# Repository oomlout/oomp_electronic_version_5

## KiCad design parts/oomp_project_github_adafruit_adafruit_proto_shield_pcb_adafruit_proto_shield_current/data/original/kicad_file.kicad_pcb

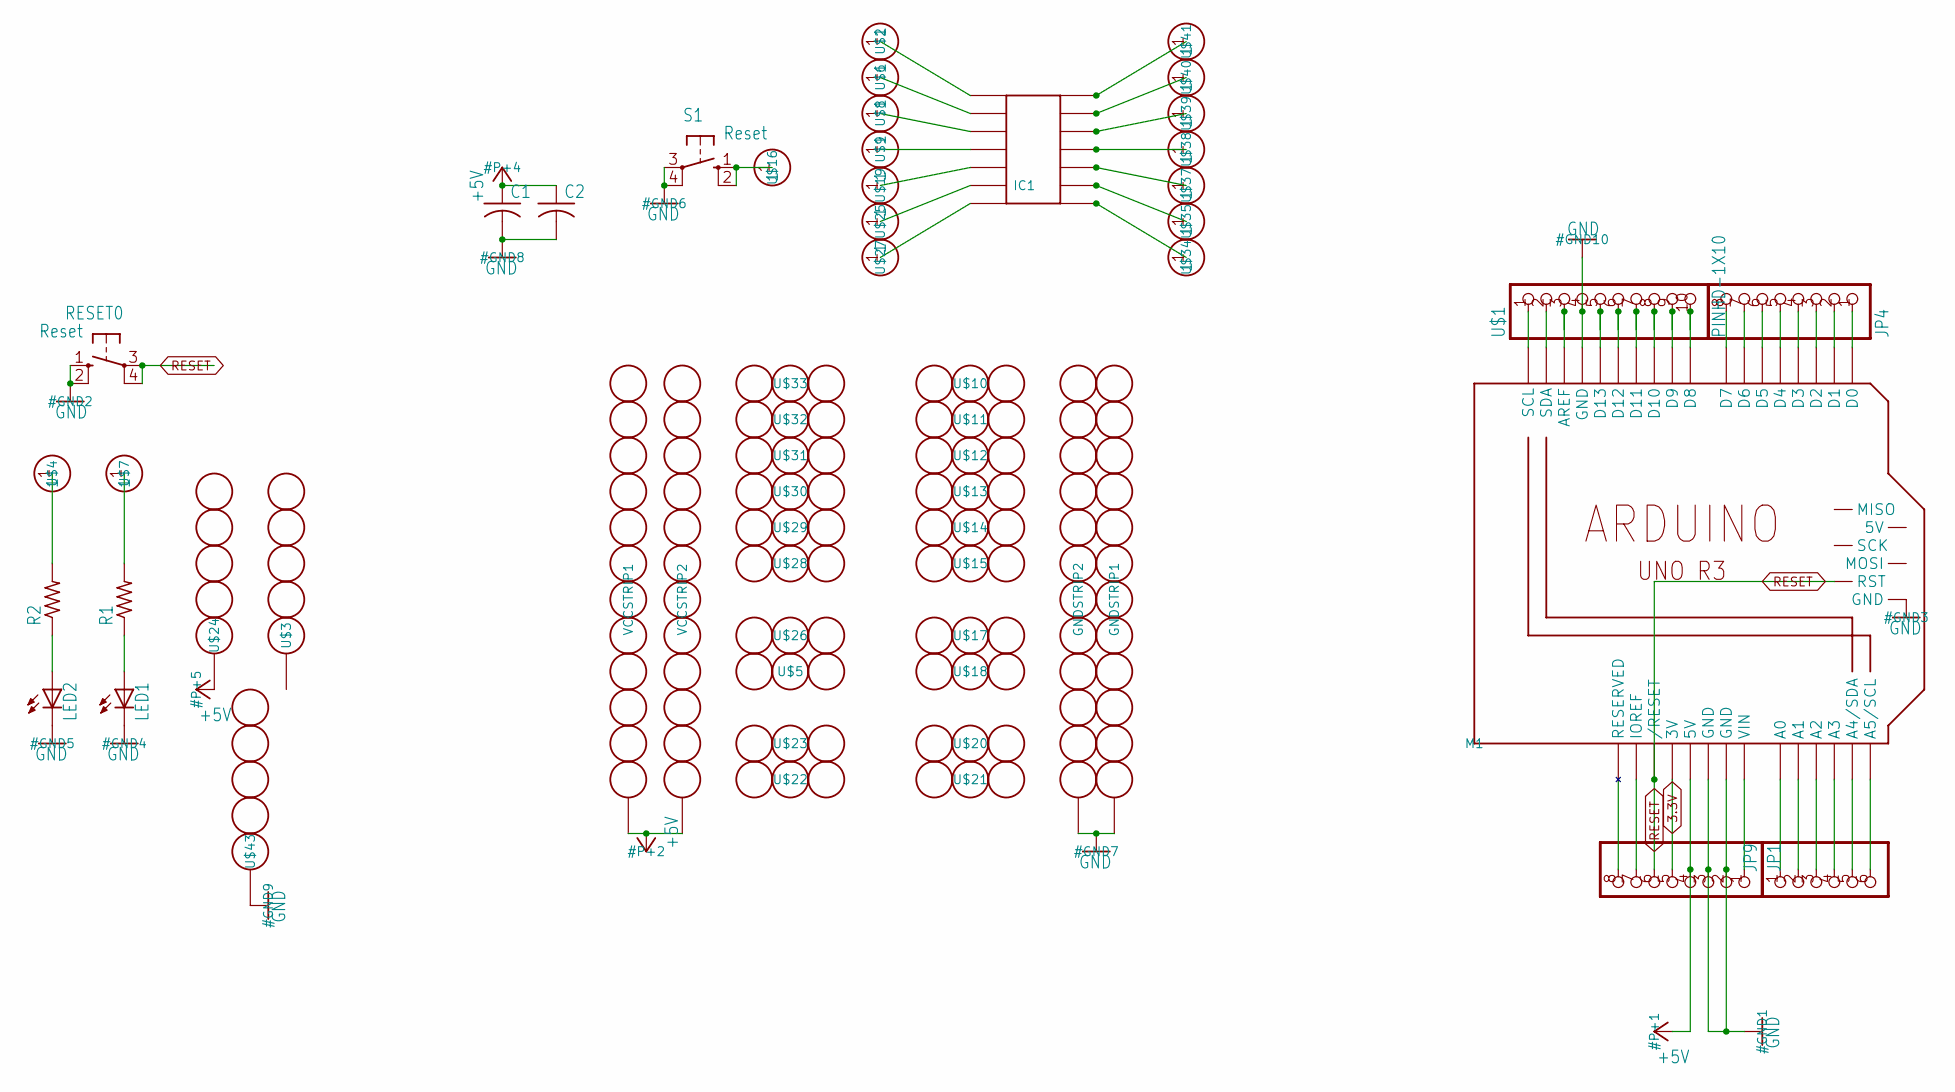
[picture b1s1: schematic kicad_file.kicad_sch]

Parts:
C1, C2: C-US025-025X050; C025-025X050
GNDSTRIP1, GNDSTRIP2: 12-STRIP
IC1: SMD-14; SO-14NMW
JP1, JP4: PINHD-1X8BIG; 1X08-BIG
JP9: PINHD-1X6B; 1X06-BIG
LED1, LED2: LED3MM
M1: ARDUINO_R3_ICSP; ARDUINOR3_ICSP
R1, R2: R-US_0207/5V; 0207_5V
RESET0: Reset; B3F-10XX
S1: Reset; B3F-10XX
U$1: PINHD-1X10; 1X10-BIG
U$2, U$4, U$6, U$7, U$8, U$9, U$16, U$19, U$25, U$27, U$34, U$35, U$37, U$38, U$39, U$40, U$41: PERFHOLE
U$3, U$24, U$43: 5-STRIP
U$5, U$10, U$11, U$12, U$13, U$14, U$15, U$17, U$18, U$20, U$21, U$22, U$23, U$26, U$28, U$29, U$30, U$31, U$32, U$33: 3-STRIP
VCCSTRIP1, VCCSTRIP2: 12-STRIP

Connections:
3.3V: JP1.5, M1.3V
+5V: C1.1, C2.1, JP1.4, M1.5V, U$24.P$3, VCCSTRIP1.P$1, VCCSTRIP2.P$1
GND: C1.2, C2.2, GNDSTRIP1.P$1, GNDSTRIP2.P$1, JP1.2, JP1.3, LED1.K (C), LED2.K (C), M1.GND, M1.GND@1 (GND), M1.GND@2 (GND), M1.GND@3 (GND), RESET0.1 (S), RESET0.2 (S1), S1.3, S1.4 (P1), U$1.4, U$43.P$3
unnamed: M1.AREF, U$1.3
unnamed: JP1.8, M1.RESERVED
unnamed: M1.D13, U$1.5
unnamed: LED1.A, R1.1
unnamed: JP1.7, M1.IOREF
unnamed: R1.2, U$7.1
unnamed: R2.2, U$4.1
unnamed: LED2.A, R2.1
unnamed: M1.D12, U$1.6
unnamed: M1.D11, U$1.7
unnamed: M1.D10, U$1.8
unnamed: M1.D9, U$1.9
unnamed: M1.D8, U$1.10
unnamed: JP9.1, M1.A0
unnamed: JP9.2, M1.A1
unnamed: JP9.3, M1.A2
unnamed: JP9.4, M1.A3
unnamed: JP9.5, M1.A4 (A4/SDA)
unnamed: JP9.6, M1.A5 (A5/SCL)
unnamed: JP4.1, M1.D0
unnamed: JP4.2, M1.D1
unnamed: JP4.3, M1.D2
unnamed: JP4.4, M1.D3
unnamed: JP4.5, M1.D4
unnamed: IC1.P$1, U$2.1
unnamed: IC1.P$2, U$6.1
unnamed: JP4.6, M1.D5
unnamed: JP4.7, M1.D6
unnamed: IC1.P$3, U$8.1
unnamed: IC1.P$4, U$9.1
unnamed: IC1.P$5, U$19.1
unnamed: JP4.8, M1.D7
unnamed: JP1.1, M1.VIN
unnamed: M1.SCL, U$1.1
unnamed: IC1.P$6, U$25.1
unnamed: IC1.P$7, U$27.1
unnamed: IC1.P$8, U$34.1
unnamed: IC1.P$9, U$35.1
unnamed: IC1.P$10, U$37.1
unnamed: M1.SDA, U$1.2
unnamed: IC1.P$11, U$38.1
unnamed: IC1.P$12, U$39.1
unnamed: IC1.P$13, U$40.1
unnamed: IC1.P$14, U$41.1
unnamed: S1.1 (S), S1.2 (S1), U$16.1
RESET: JP1.6, M1.RESET (/RESET), M1.RESET_ICSP (RST), RESET0.3, RESET0.4 (P1)

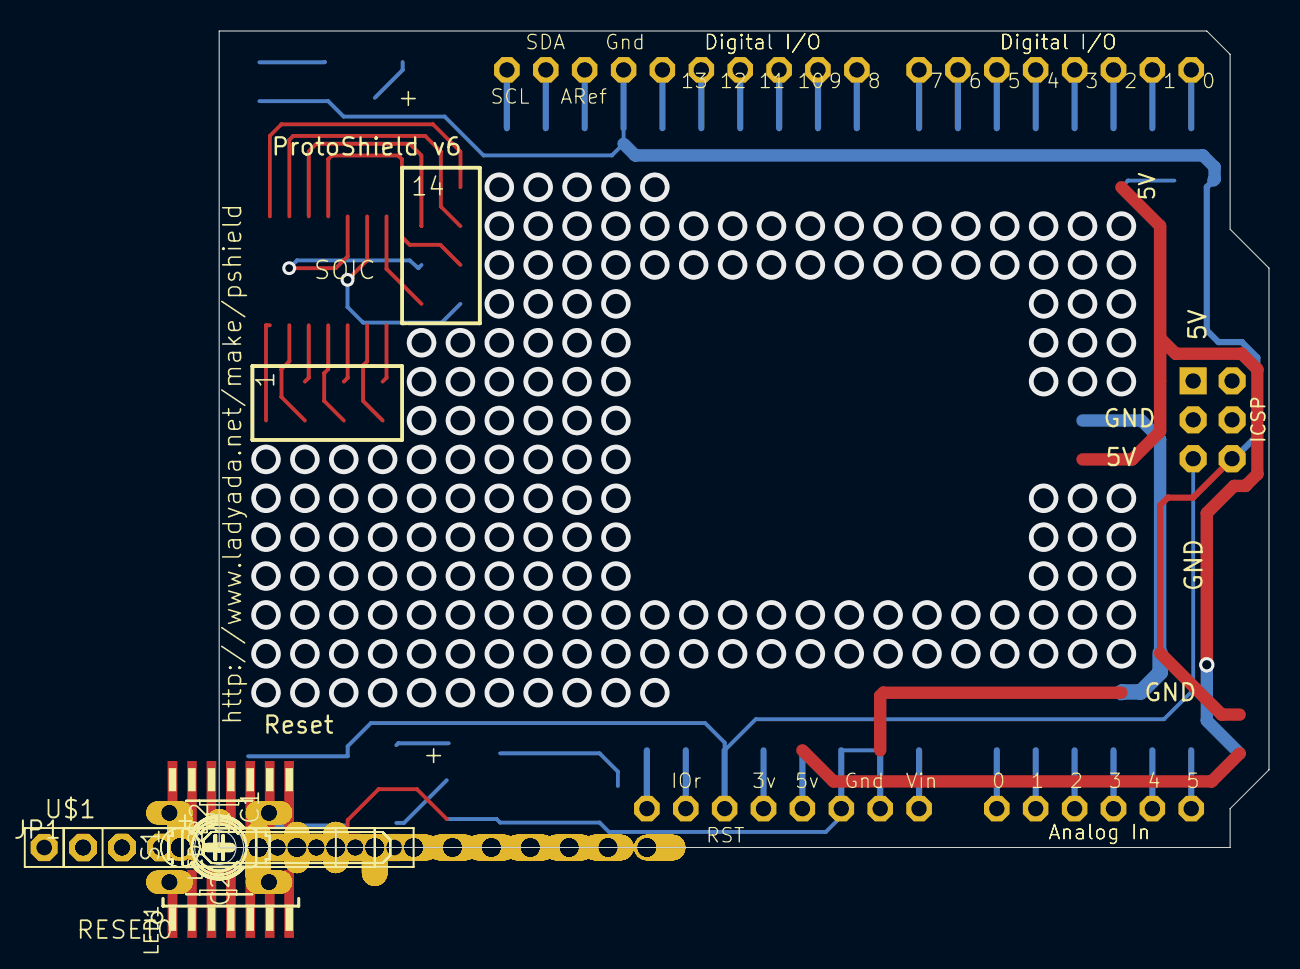
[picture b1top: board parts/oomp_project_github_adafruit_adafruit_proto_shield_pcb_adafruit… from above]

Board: 2 copper layers, 68.6 x 53.3 mm, 61 parts (1 on the bottom side), 49 nets.

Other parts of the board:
U$36: ADAFRUIT_9MM
UNK_HOLE_0: dummyfp0
UNK_HOLE_1: dummyfp1

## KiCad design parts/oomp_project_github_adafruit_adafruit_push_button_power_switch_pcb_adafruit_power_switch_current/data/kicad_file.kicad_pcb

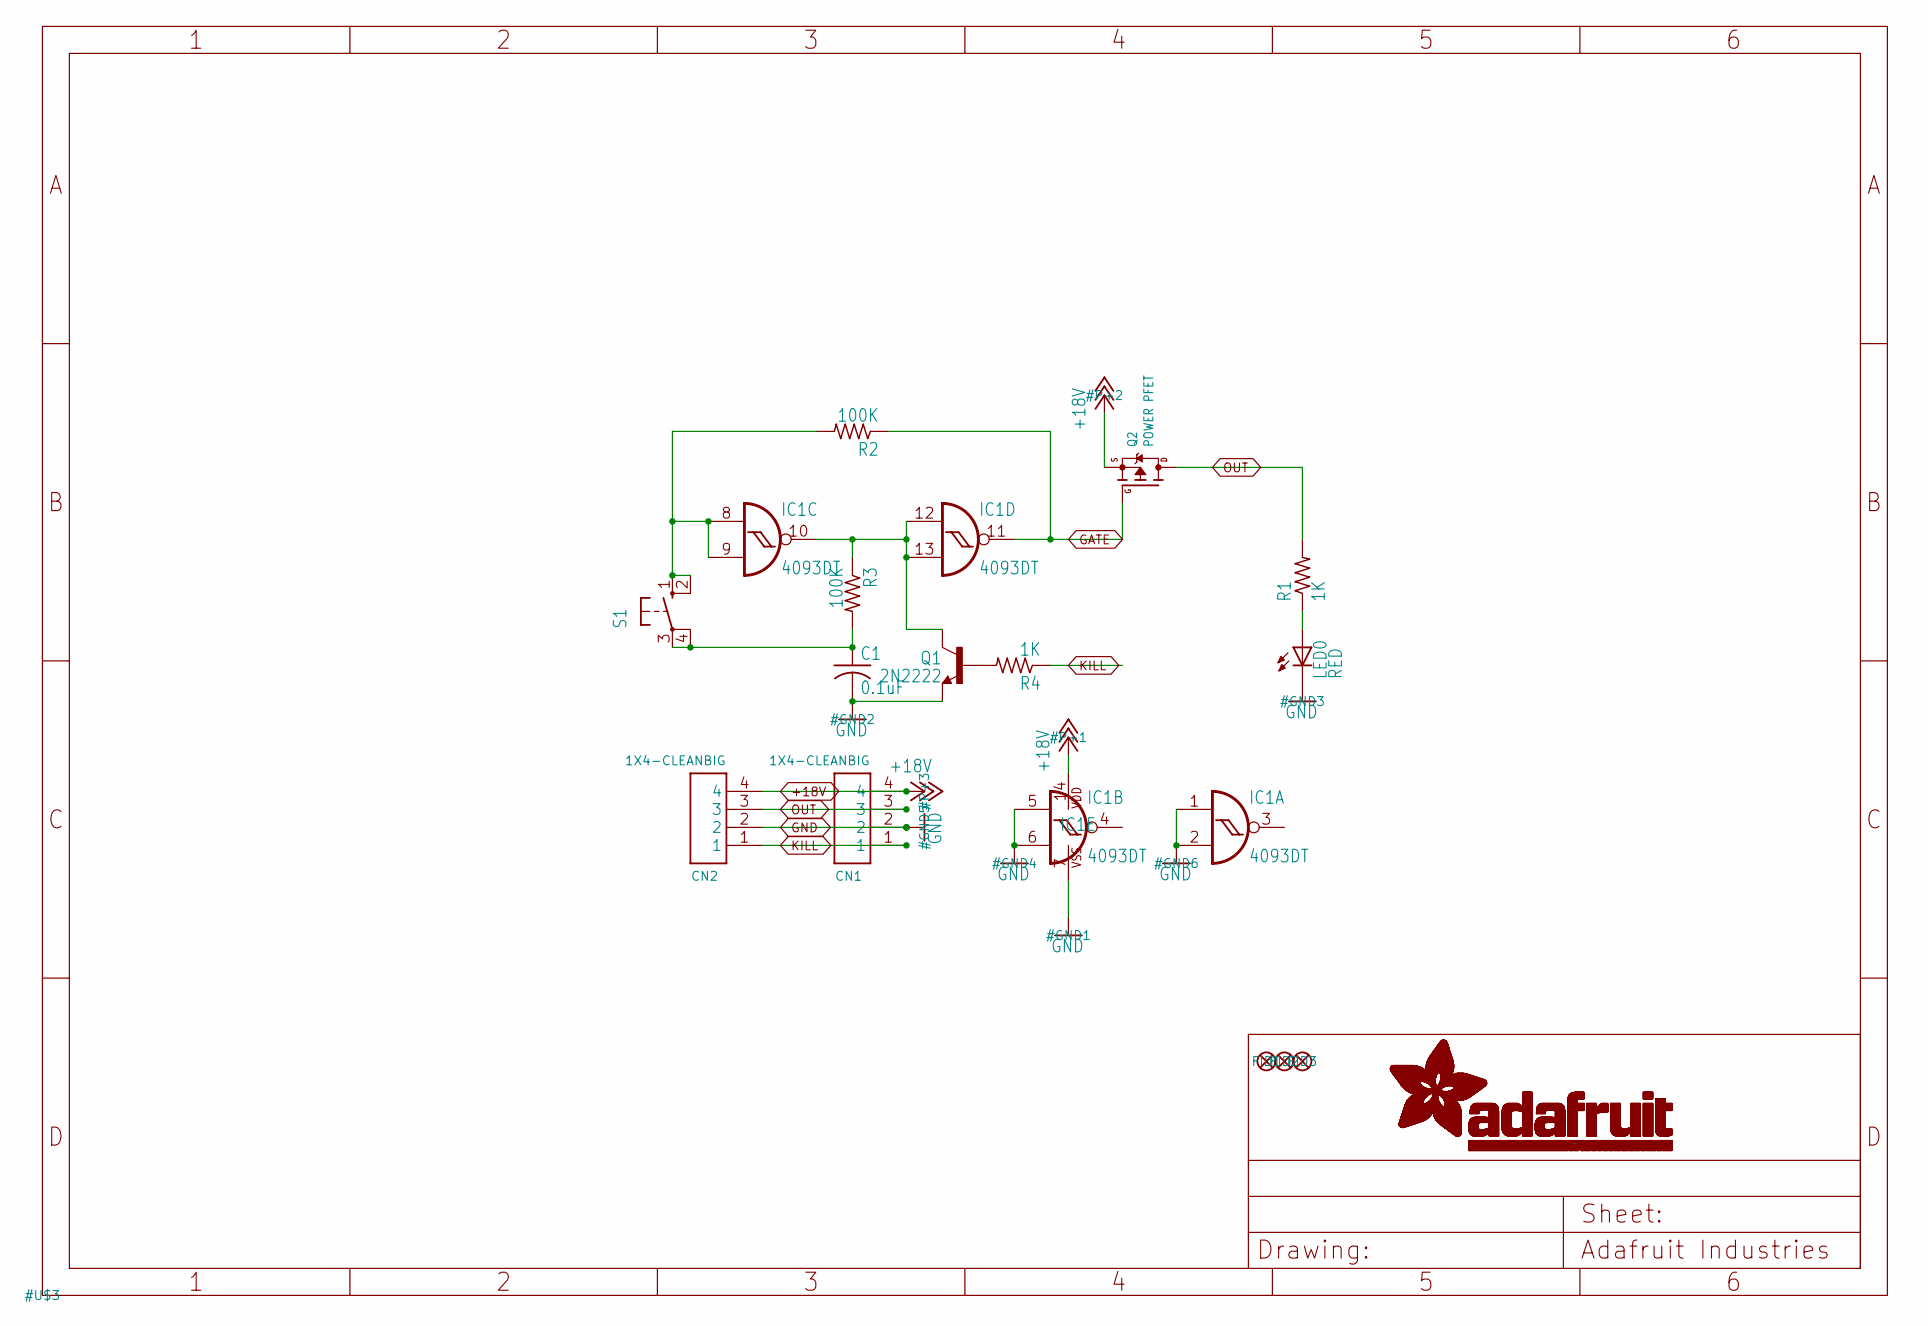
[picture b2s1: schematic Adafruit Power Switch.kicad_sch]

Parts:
C1: 0.1uF; C0805
CN1, CN2: 1X4-CLEANBIG; 1X04-CLEANBIG
FID1, FID2, FID3: FIDUCIAL""; FIDUCIAL_1MM
IC1: 4093DT; MC14093B-TSSOP14
LED0: RED; CHIP-LED0805
Q1: 2N2222; SOT23-BEC
Q2: POWER PFET; SOT23-WIDE
R1, R4: 1K; R0805
R2, R3: 100K; R0805
S1: 40-XX-ROUND; B3F-40XX-ROUND

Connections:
+18V: CN1.4, CN2.4, IC1.14 (VDD), Q2.2 (S)
GATE: IC1.11 (O), Q2.1 (G), R2.1
GND: C1.2, CN1.2, CN2.2, IC1.1 (I0), IC1.2 (I1), IC1.5 (I0), IC1.6 (I1), IC1.7 (VSS), LED0.C, Q1.E
KILL: CN1.1, CN2.1, R4.1
unnamed: Q1.B, R4.2
unnamed: IC1.10 (O), IC1.12 (I0), IC1.13 (I1), Q1.C, R3.1
unnamed: LED0.A, R1.1
unnamed: C1.1, R3.2, S1.3, S1.4 (P1)
unnamed: IC1.8 (I0), IC1.9 (I1), R2.2, S1.1 (S), S1.2 (S1)
OUT: CN1.3, CN2.3, Q2.3 (D), R1.2

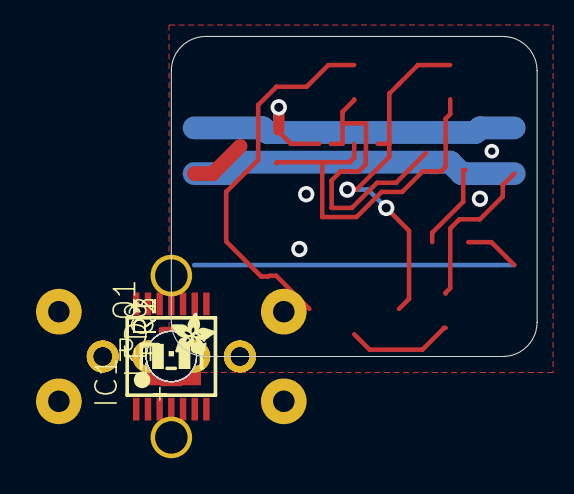
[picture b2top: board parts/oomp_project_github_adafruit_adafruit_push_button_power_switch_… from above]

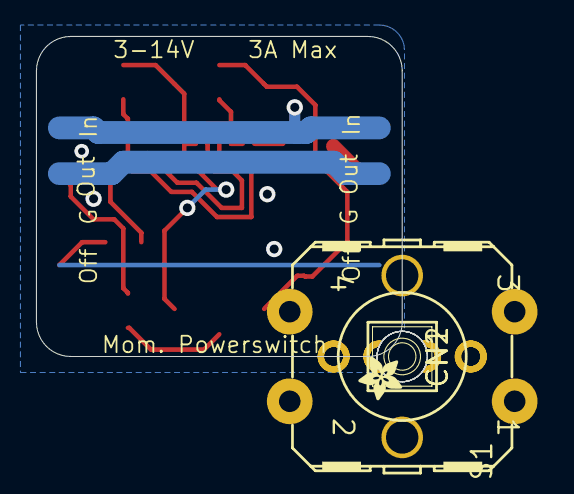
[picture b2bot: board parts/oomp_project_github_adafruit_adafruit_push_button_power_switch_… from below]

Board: 2 copper layers, 20.3 x 17.8 mm, 21 parts (4 on the bottom side), 10 nets.

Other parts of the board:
U$1, U$2: ADAFRUIT_2.5MM
UNK_HOLE_0: dummyfp0
UNK_HOLE_1: dummyfp1
UNK_HOLE_2: dummyfp2
UNK_HOLE_3: dummyfp3

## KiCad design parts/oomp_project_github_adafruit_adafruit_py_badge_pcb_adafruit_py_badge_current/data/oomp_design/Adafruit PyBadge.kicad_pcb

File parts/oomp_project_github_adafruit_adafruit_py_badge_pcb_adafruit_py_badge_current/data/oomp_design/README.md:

# OOMP KiCad design copy

Open `Adafruit PyBadge.kicad_pro` (or the `.kicad_pcb` / `.kicad_sch`) in KiCad. Local OOMP libraries are under `libraries/`. Original inputs are preserved in [../original/](../original/).

Only verified unchanged installed KiCad defaults were renamed. Modified, custom, unmatched and unavailable items remain unchanged. Soldering variants are never swapped during conversion. Existing pad coordinates, nets and UUIDs are preserved.

See [conversion_report.yaml](conversion_report.yaml) for every conversion and skip. Copy this directory before editing; regeneration refuses to overwrite edited design files.

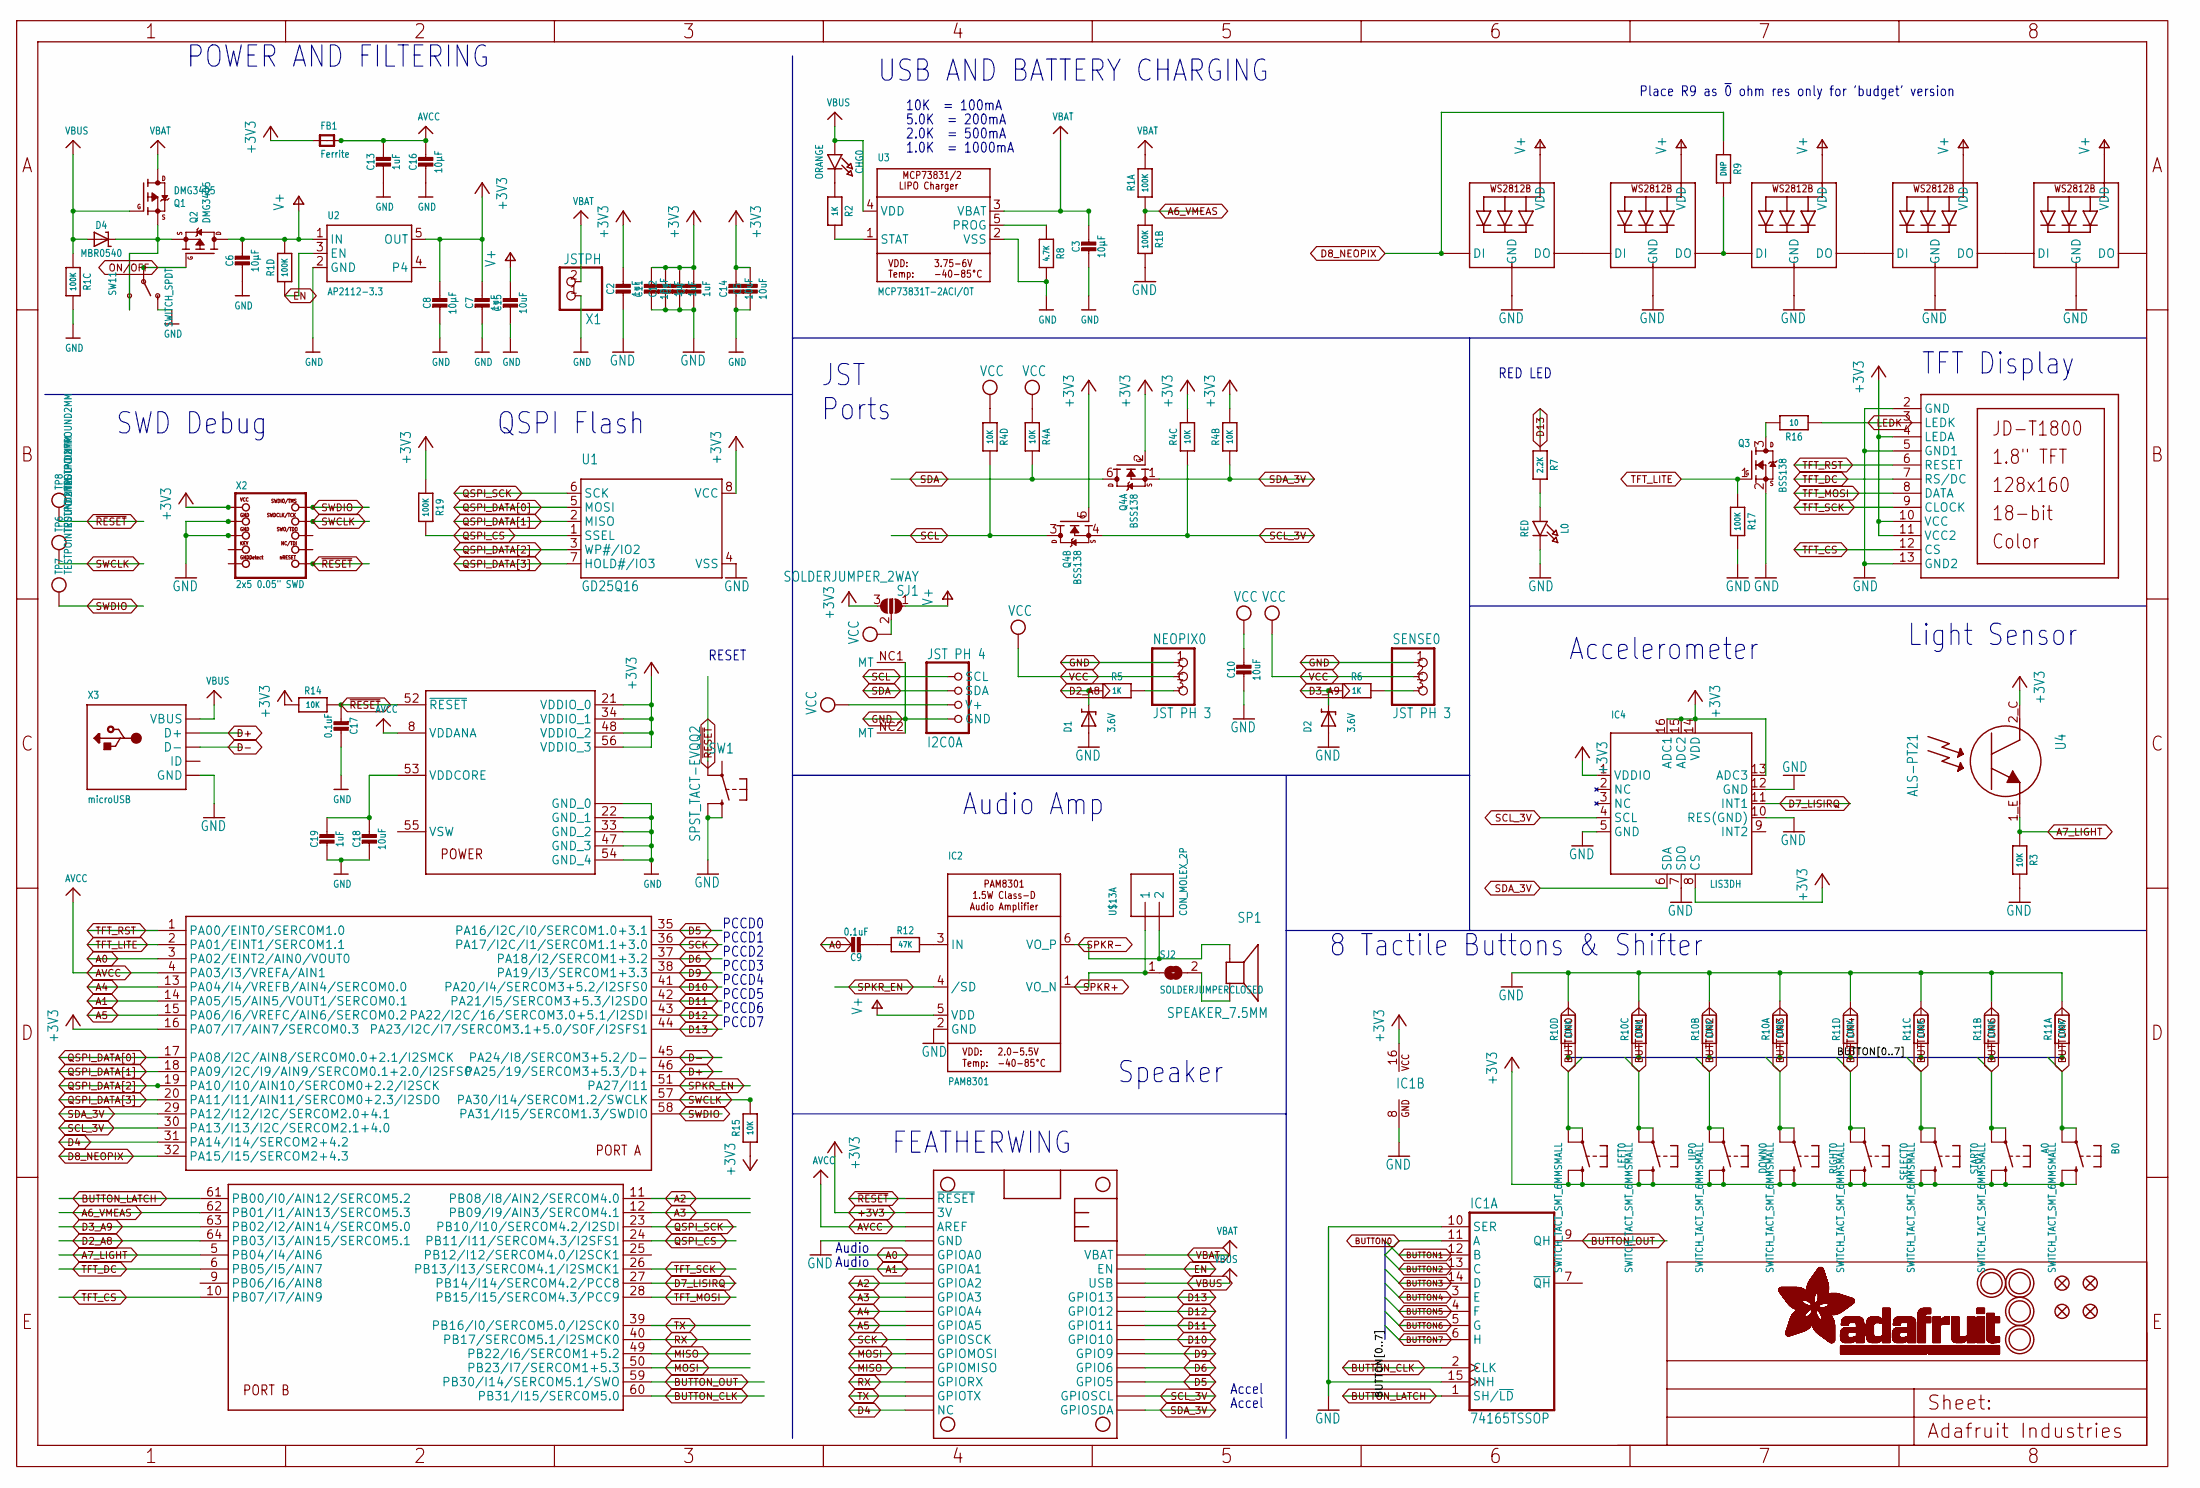
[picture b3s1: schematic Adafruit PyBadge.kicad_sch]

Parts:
A0: SWITCH_TACT_SMT_6MMSMALL; 6MM_SMT
B0: SWITCH_TACT_SMT_6MMSMALL; 6MM_SMT
C1, C2, C4, C7, C12, C13, C19: 1uF; 0603-NO
C3, C6, C8: 10µF; 0805-NO
C5, C10, C11, C14, C15, C18: 10uF; 0805-NO
C9, C17: 0.1uF; 0603-NO
C16: 10µF; _0805MP
CHG0: ORANGE; CHIPLED_0805_NOOUTLINE
D1, D2: 3.6V; SOD-323
D4: MBR0540; SOD-123
DOWN0: SWITCH_TACT_SMT_6MMSMALL; 6MM_SMT
FB1: Ferrite; 0805-NO
I2C0: JST PH 4; JSTPH4
IC1: 74165TSSOP; TSSOP16
IC2: PAM8301; SOT23-6
IC4: LIS3DH; LGA16_3X3MM
L0: RED; CHIPLED_0805_NOOUTLINE
LCD1: DISP_LCD_JDT1800; JD-T1800
LED1, LED2, LED3, LED4, LED5: WS2812B3535; LED3535
LEFT0: SWITCH_TACT_SMT_6MMSMALL; 6MM_SMT
MS1: FEATHERWING_SMTDUALNOHOLES; FEATHERWING_SMT_NOHOLES
NEOPIX0: JST PH 3; JSTPH3
Q1, Q2: DMG3405; SOT23-R
Q3: BSS138; SOT23-WIDE
Q4: BSS138; SOT363
R1, R10, R11: 100K; RESPACK_4X0603
R2, R5, R6: 1K; 0603-NO
R3, R14, R15: 10K; 0603-NO
R4: 10K; RESPACK_4X0603
R7: 2.2K; 0603-NO
R8: 4.7K; 0603-NO
R9: DNP; 0603-NO
R12: 47K; 0603-NO
R16: 10; 0603-NO
R17, R19: 100K; 0603-NO
RIGHT0: SWITCH_TACT_SMT_6MMSMALL; 6MM_SMT
SELECT0: SWITCH_TACT_SMT_6MMSMALL; 6MM_SMT
SENSE0: JST PH 3; JSTPH3
SJ1: SOLDERJUMPER_2WAY; SOLDERJUMPER_2WAY_OPEN_NOPASTE
SJ2: SOLDERJUMPERCLOSED; SOLDERJUMPER_CLOSEDWIRE
SP1: SPEAKER_7.5MM; BUZZER_SMT_7.5MM
START0: SWITCH_TACT_SMT_6MMSMALL; 6MM_SMT
SW1: SPST_TACT-EVQQ2; EVQ-Q2_SMALLER
SW11: SWITCH_SPDT; SPDT_SMT_SSSS811101
TP6, TP7, TP8: TESTPOINTROUND2MM; TESTPOINT_ROUND_2MM
U1: GD25Q16; SOIC8_208MIL
U2: AP2112-3.3; SOT23-5
U3: MCP73831T-2ACI/OT; SOT23-5
U4: ALS-PT21; ALS-PT26-21C
U$5, U$6, U$15, U$17: MOUNTINGHOLE3.0THIN; MOUNTINGHOLE_3.0_PLATEDTHIN
U$13: CON_MOLEX_2P; 53398-0271
U$24: ATSAMD51J19; PQFN64-1
U$34, U$35, U$42, U$43: FIDUCIAL_1MM
UP0: SWITCH_TACT_SMT_6MMSMALL; 6MM_SMT
X1: JSTPH; JSTPH2
X2: 2x5 0.05" SWD; 2X05_1.27MM_BOX_POSTS
X3: microUSB; 4UCONN_20329_V2

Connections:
+3V3: A0.B (S), A0.B' (S1), B0.B (S), B0.B' (S1), C1.1, C2.1, C4.1, C5.1, C7.1, C8.1, C11.1, C12.1, C14.1, DOWN0.B (S), DOWN0.B' (S1), FB1.1, IC1.16 (VCC), IC4.1 (VDDIO), IC4.8 (CS), IC4.13 (ADC3), IC4.14 (VDD), IC4.15 (ADC2), IC4.16 (ADC1), LCD1.4 (LEDA), LCD1.10 (VCC), LCD1.11 (VCC2), LEFT0.B (S), LEFT0.B' (S1), MS1.2 (3V), MS1.2B (3V), Q4.2 (G), Q4.5 (G), R4.2 (1), R4.3 (1), R14.1, R15.1, R19.1, RIGHT0.B (S), RIGHT0.B' (S1), SELECT0.B (S), SELECT0.B' (S1), SJ1.3, START0.B (S), START0.B' (S1), U1.8 (VCC), U2.5 (OUT), U4.2_C (C), U$24.16 (PA07/I7/AIN7/SERCOM0.3), U$24.21 (VDDIO_0), U$24.34 (VDDIO_1), U$24.48 (VDDIO_2), U$24.56 (VDDIO_3), UP0.B (S), UP0.B' (S1), X2.1 (VCC)
A0: C9.1, MS1.5 (GPIOA0), MS1.5B (GPIOA0), U$24.3 (PA02/EINT2/AIN0/VOUT0)
A1: MS1.6 (GPIOA1), MS1.6B (GPIOA1), U$24.14 (PA05/I5/AIN5/VOUT1/SERCOM0.1)
A2: MS1.7 (GPIOA2), MS1.7B (GPIOA2), U$24.11 (PB08/I8/AIN2/SERCOM4.0)
A3: MS1.8 (GPIOA3), MS1.8B (GPIOA3), U$24.12 (PB09/I9/AIN3/SERCOM4.1)
A4: MS1.9 (GPIOA4), MS1.9B (GPIOA4), U$24.13 (PA04/I4/VREFB/AIN4/SERCOM0.0)
A5: MS1.10 (GPIOA5), MS1.10B (GPIOA5), U$24.15 (PA06/I6/VREFC/AIN6/SERCOM0.2)
A6_VMEAS: R1.1, R1.2 (1), U$24.62 (PB01/I1/AIN13/SERCOM5.3)
A7_LIGHT: R3.2, U4.1_E (E), U$24.5 (PB04/I4/AIN6)
AVCC: C13.1, C16.1, FB1.2, MS1.3 (AREF), MS1.3B (AREF), U$24.4 (PA03/I3/VREFA/AIN1), U$24.8 (VDDANA)
BUTTON0: IC1.11 (A), LEFT0.A, LEFT0.A' (P1), R10.4 (1)
BUTTON1: IC1.12 (B), R10.3 (1), UP0.A, UP0.A' (P1)
BUTTON2: DOWN0.A, DOWN0.A' (P1), IC1.13 (C), R10.2 (1)
BUTTON3: IC1.14 (D), R10.1, RIGHT0.A, RIGHT0.A' (P1)
BUTTON4: IC1.3 (E), R11.4 (1), SELECT0.A, SELECT0.A' (P1)
BUTTON5: IC1.4 (F), R11.3 (1), START0.A, START0.A' (P1)
BUTTON6: A0.A, A0.A' (P1), IC1.5 (G), R11.2 (1)
BUTTON7: B0.A, B0.A' (P1), IC1.6 (H), R11.1
BUTTON_CLK: IC1.2 (CLK), U$24.60 (PB31/I15/SERCOM5.0)
BUTTON_LATCH: IC1.1 (SH/~LD), U$24.61 (PB00/I0/AIN12/SERCOM5.2)
BUTTON_OUT: IC1.9 (QH), U$24.59 (PB30/I14/SERCOM5.1/SWO)
CHG_LED: R2.2, U3.1 (STAT)
CHG_RATE: R8.1, U3.5 (PROG)
D2_: NEOPIX0.3, R5.1
D2_A8: D1.C, R5.2, U$24.64 (PB03/I3/AIN15/SERCOM5.1)
D3_: R6.1, SENSE0.3
D3_A9: D2.C, R6.2, U$24.63 (PB02/I2/AIN14/SERCOM5.0)
D4: MS1.16 (NC), MS1.16B (NC), U$24.31 (PA14/I14/SERCOM2+4.2)
D5: MS1.19 (GPIO5), MS1.19B (GPIO5), U$24.35 (PA16/I2C/I0/SERCOM1.0+3.1)
D6: MS1.20 (GPIO6), MS1.20B (GPIO6), U$24.37 (PA18/I2/SERCOM1+3.2)
D7_LISIRQ: IC4.11 (INT1), U$24.27 (PB14/I14/SERCOM4.2/PCC8)
D8_NEOPIX: LED1.1 (DI), R9.1, U$24.32 (PA15/I15/SERCOM2+4.3)
D9: MS1.21 (GPIO9), MS1.21B (GPIO9), U$24.38 (PA19/I3/SERCOM1+3.3)
D10: MS1.22 (GPIO10), MS1.22B (GPIO10), U$24.41 (PA20/I4/SERCOM3+5.2/I2SFS0)
D11: MS1.23 (GPIO11), MS1.23B (GPIO11), U$24.42 (PA21/I5/SERCOM3+5.3/I2SDO)
D12: MS1.24 (GPIO12), MS1.24B (GPIO12), U$24.43 (PA22/I2C/16/SERCOM3.0+5.1/I2SDI)
D13: MS1.25 (GPIO13), MS1.25B (GPIO13), R7.1, U$24.44 (PA23/I2C/I7/SERCOM3.1+5.0/SOF/I2SFS1)
D+: U$24.46 (PA25/19/SERCOM3+5.3/D+), X3.D+
D-: U$24.45 (PA24/I8/SERCOM3+5.2/D-), X3.D-
EN: MS1.27 (EN), MS1.27B (EN), R1.4 (1), U2.3 (EN)
GND: C1.2, C2.2, C3.2, C4.2, C5.2, C6.2, C7.2, C8.2, C10.2, C11.2, C12.2, C13.2, C14.2, C15.2, C16.2, C17.1, C18.2, C19.2, D1.A, D2.A, I2C0.1 (GND), I2C0.NC1 (MT), I2C0.NC2 (MT), IC1.8 (GND), IC1.10 (SER), IC1.15 (INH), IC2.2 (GND), IC4.5 (GND), IC4.7 (SDO), IC4.10 (RES(GND)), IC4.12 (GND), L0.C, LCD1.2 (GND), LCD1.5 (GND1), LCD1.13 (GND2), LED1.4 (GND), LED2.4 (GND), LED3.4 (GND), LED4.4 (GND), LED5.4 (GND), MS1.4 (GND), MS1.4B (GND), NEOPIX0.1, Q3.2 (S), R1.6 (2), R1.7 (2), R3.1, R8.2, R10.5 (2), R10.6 (2), R10.7 (2), R10.8 (2), R11.5 (2), R11.6 (2), R11.7 (2), R11.8 (2), R17.2, SENSE0.1, SW1.B (S), SW1.B' (S1), SW11.A (O), U1.4 (VSS), U2.2 (GND), U3.2 (VSS), U$24.7 (GND_0), U$24.22 (GND_1), U$24.33 (GND_2), U$24.47 (GND_3), U$24.54 (GND_4), U$24.EXP (GND_0), X1.1, X2.3 (GND), X2.5 (GND), X3.BASE@1 (GND), X3.BASE@2 (GND), X3.GND, X3.SPRT@1 (GND), X3.SPRT@2 (GND), X3.SPRT@3 (GND), X3.SPRT@4 (GND)
LEDK: LCD1.3 (LEDK), R16.1
MISO: MS1.13 (GPIOMISO), MS1.13B (GPIOMISO), U$24.49 (PB22/I6/SERCOM1+5.2)
MOSI: MS1.12 (GPIOMOSI), MS1.12B (GPIOMOSI), U$24.50 (PB23/I7/SERCOM1+5.3)
unnamed: CHG0.C, R2.1
unnamed: L0.A, R7.2
unnamed: LED1.3 (DO), LED2.1 (DI)
unnamed: LED2.3 (DO), LED3.1 (DI), R9.2
unnamed: LED3.3 (DO), LED4.1 (DI)
unnamed: Q3.3 (D), R16.2
unnamed: LED4.3 (DO), LED5.1 (DI)
unnamed: D4.C, Q1.2 (S), Q2.2 (S), SW11.C (S)
unnamed: C9.2, R12.1
unnamed: IC2.3 (IN), R12.2
unnamed: SJ2.2, SP1.-
ON/OFF: Q2.1 (G), SW11.B
QSPI_CS: R19.2, U1.1 (SSEL), U$24.24 (PB11/I11/SERCOM4.3/I2SFS1)
QSPI_DATA[0]: U1.5 (MOSI), U$24.17 (PA08/I2C/AIN8/SERCOM0.0+2.1/I2SMCK)
QSPI_DATA[1]: U1.2 (MISO), U$24.18 (PA09/I2C/I9/AIN9/SERCOM0.1+2.0/I2SFS0)
QSPI_DATA[2]: U1.3 (WP#/IO2), U$24.19 (PA10/I10/AIN10/SERCOM0+2.2/I2SCK)
QSPI_DATA[3]: U1.7 (HOLD#/IO3), U$24.20 (PA11/I11/AIN11/SERCOM0+2.3/I2SDO)
QSPI_SCK: U1.6 (SCK), U$24.23 (PB10/I10/SERCOM4.2/I2SDI)
RX: MS1.14 (GPIORX), MS1.14B (GPIORX), U$24.40 (PB17/SERCOM5.1/I2SMCK0)
SCK: MS1.11 (GPIOSCK), MS1.11B (GPIOSCK), U$24.36 (PA17/I2C/I1/SERCOM1.1+3.0)
SCL: I2C0.4 (SCL), Q4.3 (D), R4.5 (2)
SCL_3V: IC4.4 (SCL), MS1.18 (GPIOSCL), MS1.18B (GPIOSCL), Q4.4 (S), R4.6 (2), U$24.30 (PA13/I13/I2C/SERCOM2.1+4.0)
SDA: I2C0.3 (SDA), Q4.6 (D), R4.8 (2)
SDA_3V: IC4.6 (SDA), MS1.17 (GPIOSDA), MS1.17B (GPIOSDA), Q4.1 (S), R4.7 (2), U$24.29 (PA12/I12/I2C/SERCOM2.0+4.1)
SPKR+: IC2.1 (VO_N), SJ2.1, U$13.1
SPKR-: IC2.6 (VO_P), SP1.+, U$13.2
SPKR_EN: IC2.4 (/SD), U$24.51 (PA27/I11)
SWCLK: R15.2, TP6.P$1, U$24.57 (PA30/I14/SERCOM1.2/SWCLK), X2.4 (SWDCLK)
SWDIO: TP7.P$1, U$24.58 (PA31/I15/SERCOM1.3/SWDIO), X2.2 (SWDIO)
TFT_CS: LCD1.12 (CS), U$24.10 (PB07/I7/AIN9)
TFT_DC: LCD1.7 (RS/DC), U$24.6 (PB05/I5/AIN7)
TFT_LITE: Q3.1 (G), R17.1, U$24.2 (PA01/EINT1/SERCOM1.1)
TFT_MOSI: LCD1.8 (DATA), U$24.28 (PB15/I15/SERCOM4.3/PCC9)
TFT_RST: LCD1.6 (RESET), U$24.1 (PA00/EINT0/SERCOM1.0)
TFT_SCK: LCD1.9 (CLOCK), U$24.26 (PB13/I13/SERCOM4.1/I2SMCK1)
TX: MS1.15 (GPIOTX), MS1.15B (GPIOTX), U$24.39 (PB16/I0/SERCOM5.0/I2SCK0)
V+: C6.1, C15.1, IC2.5 (VDD), LED1.2 (VDD), LED2.2 (VDD), LED3.2 (VDD), LED4.2 (VDD), LED5.2 (VDD), Q2.3 (D), R1.5 (2), SJ1.1, U2.1 (IN)
VBAT: C3.1, MS1.28 (VBAT), MS1.28B (VBAT), Q1.3 (D), R1.8 (2), U3.3 (VBAT), X1.2
VBUS: CHG0.A, D4.A, MS1.26 (USB), MS1.26B (USB), Q1.1 (G), R1.3 (1), U3.4 (VDD), X3.VBUS
VCC: C10.1, I2C0.2 (V+), NEOPIX0.2, R4.1, R4.4 (1), SENSE0.2, SJ1.2
VDDCORE2: C18.1, C19.1, U$24.53 (VDDCORE)
~RESET: C17.2, MS1.1 (~RESET), MS1.1B (~RESET), R14.2, SW1.A' (P1), TP8.P$1, U$24.52 (~RESET), X2.10 (NRESET)

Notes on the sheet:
PCCD6
PCCD3
Place R9 as ~{0} ohm res only for 'budget' version
10K = 100mA
PCCD2
SWD Debug
Audio Amp
Accel
QSPI Flash
USB AND BATTERY CHARGING
JST Ports
FEATHERWING
1.0K = 1000mA
Speaker
8 Tactile Buttons & Shifter
5.0K = 200mA
Audio
PCCD5
PCCD7
Light Sensor
2.0K = 500mA
PCCD4
RED LED
PCCD1
Accelerometer
TFT Display
RESET
POWER AND FILTERING
PCCD0

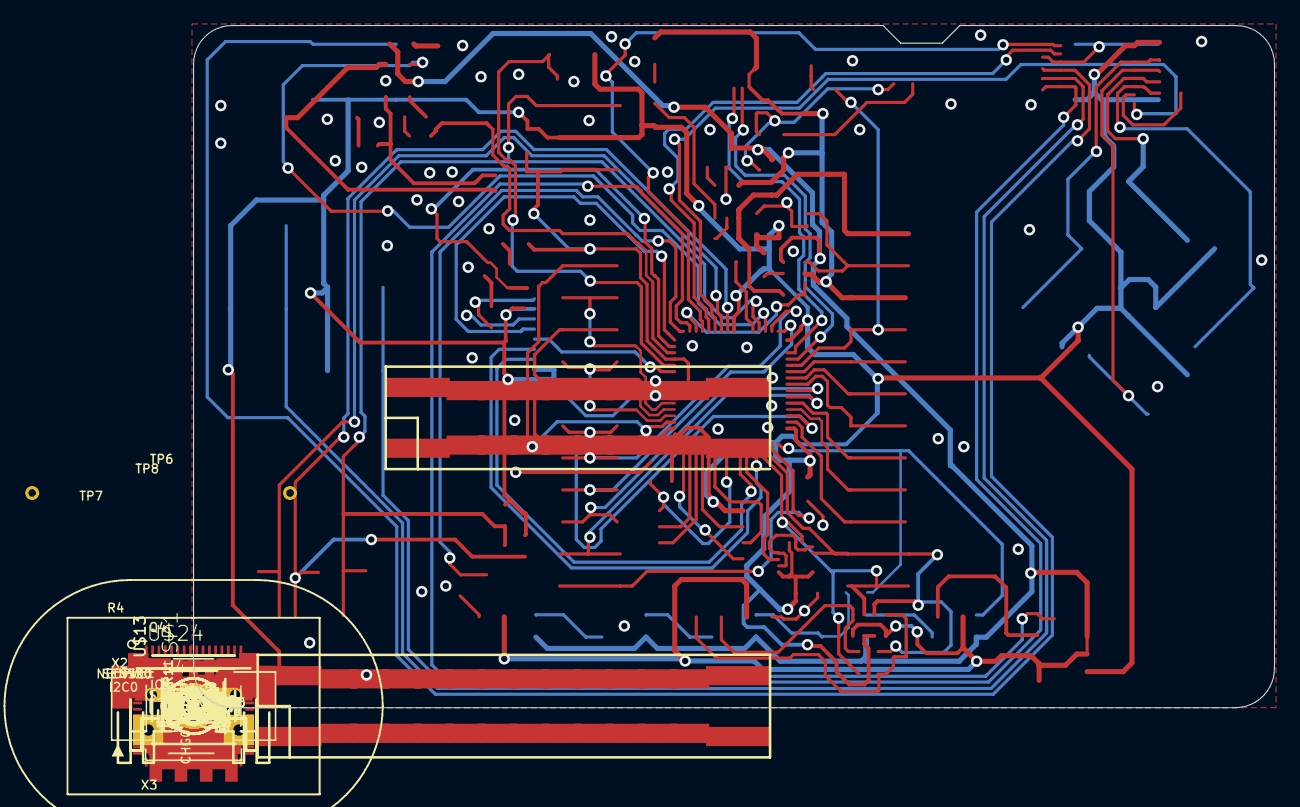
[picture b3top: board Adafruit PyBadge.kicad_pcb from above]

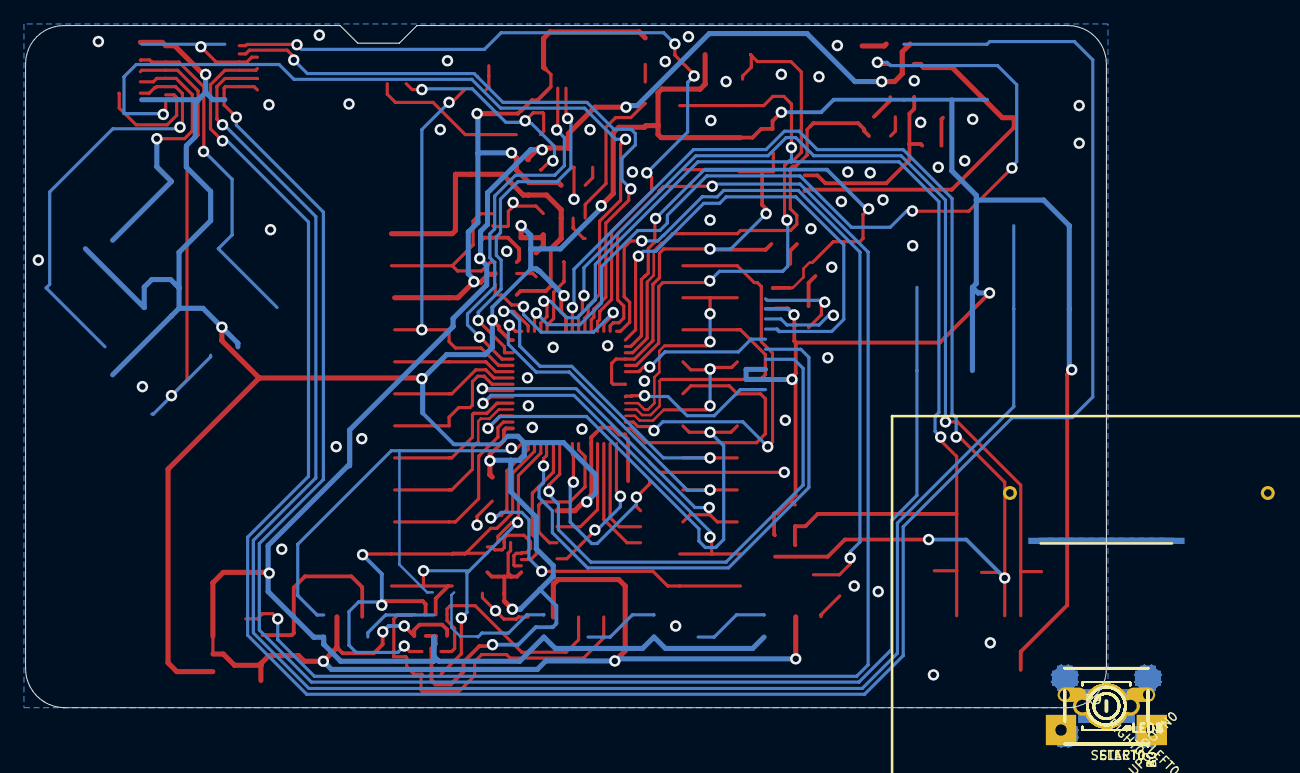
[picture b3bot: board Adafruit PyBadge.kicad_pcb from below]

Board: 2 copper layers, 85.7 x 54.1 mm, 96 parts (18 on the bottom side), 86 nets.

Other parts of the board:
U$8: SPEAKER_OVAL8OHM
U$18: PYBADGE_TOP
U$32: PYBADGE_BOT
U$37: PCBFEAT-REV-040

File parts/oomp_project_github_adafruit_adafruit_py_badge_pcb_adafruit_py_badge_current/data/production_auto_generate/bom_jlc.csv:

Comment,Designator,Footprint,LCSC Part #
,"A0,B0,DOWN0,LEFT0,RIGHT0,SELECT0,START0,UP0",Adafruit PyBadge-import-fps:6MM_SMT,
,U$37,Adafruit PyBadge-import-fps:PCBFEAT-REV-040,
,U$32,Adafruit PyBadge-import-fps:PYBADGE_BOT,
,U$18,Adafruit PyBadge-import-fps:PYBADGE_TOP,
,SW11,Adafruit PyBadge-import-fps:SPDT_SMT_SSSS811101,
,U$8,Adafruit PyBadge-import-fps:SPEAKER_OVAL8OHM,
,"TP6,TP7,TP8",Adafruit PyBadge-import-fps:TESTPOINT_ROUND_2MM,
0.1uF,"C9,C17",Adafruit PyBadge-import-fps:0603-NO,C14663
10,R16,Adafruit PyBadge-import-fps:0603-NO,C22859
100K,"R17,R19",Adafruit PyBadge-import-fps:0603-NO,C25803
100K,"R1,R10,R11",Adafruit PyBadge-import-fps:RESPACK_4X0603,C25803
10K,"R3,R14,R15",Adafruit PyBadge-import-fps:0603-NO,C98220
10K,R4,Adafruit PyBadge-import-fps:RESPACK_4X0603,C98220
10uF,"C5,C10,C11,C14,C15,C18",Adafruit PyBadge-import-fps:0805-NO,
10µF,"C3,C6,C8",Adafruit PyBadge-import-fps:0805-NO,
10µF,C16,Adafruit PyBadge-import-fps:_0805MP,
1K,"R2,R5,R6",Adafruit PyBadge-import-fps:0603-NO,C2907002
1uF,"C1,C2,C4,C7,C12,C13,C19",Adafruit PyBadge-import-fps:0603-NO,C5673
2.2K,R7,Adafruit PyBadge-import-fps:0603-NO,C4190
"2x5 0.05"" SWD",X2,Adafruit PyBadge-import-fps:2X05_1.27MM_BOX_POSTS,
3.6V,"D1,D2",Adafruit PyBadge-import-fps:SOD-323,
4.7K,R8,Adafruit PyBadge-import-fps:0603-NO,C23162
47K,R12,Adafruit PyBadge-import-fps:0603-NO,C2907042
74165TSSOP,IC1,Adafruit PyBadge-import-fps:TSSOP16,
ALS-PT21,U4,Adafruit PyBadge-import-fps:ALS-PT26-21C,
AP2112-3.3,U2,Adafruit PyBadge-import-fps:SOT23-5,
ATSAMD51J19,U$24,Adafruit PyBadge-import-fps:PQFN64-1,
BSS138,Q3,Adafruit PyBadge-import-fps:SOT23-WIDE,C52895
BSS138,Q4,Adafruit PyBadge-import-fps:SOT363,
CON_MOLEX_2P,U$13,Adafruit PyBadge-import-fps:53398-0271,
DISP_LCD_JDT1800,LCD1,Adafruit PyBadge-import-fps:JD-T1800,
DMG3405,"Q1,Q2",Adafruit PyBadge-import-fps:SOT23-R,
DNP,R9,Adafruit PyBadge-import-fps:0603-NO,
FEATHERWING_SMTDUALNOHOLES,MS1,Adafruit PyBadge-import-fps:FEATHERWING_SMT_NOHOLES,
Ferrite,FB1,Adafruit PyBadge-import-fps:0805-NO,
FIDUCIAL_1MM,"U$34,U$35,U$42,U$43",Adafruit PyBadge-import-fps:FIDUCIAL_1MM,
GD25Q16,U1,Adafruit PyBadge-import-fps:SOIC8_208MIL,
JST PH 3,"NEOPIX0,SENSE0",Adafruit PyBadge-import-fps:JSTPH3,
JST PH 4,I2C0,Adafruit PyBadge-import-fps:JSTPH4,
JSTPH,X1,Adafruit PyBadge-import-fps:JSTPH2,
LIS3DH,IC4,Adafruit PyBadge-import-fps:LGA16_3X3MM,
MBR0540,D4,Adafruit PyBadge-import-fps:SOD-123,
MCP73831T-2ACI/OT,U3,Adafruit PyBadge-import-fps:SOT23-5,
microUSB,X3,Adafruit PyBadge-import-fps:4UCONN_20329_V2,
ORANGE,CHG0,Adafruit PyBadge-import-fps:CHIPLED_0805_NOOUTLINE,
PAM8301,IC2,Adafruit PyBadge-import-fps:SOT23-6,
RED,L0,Adafruit PyBadge-import-fps:CHIPLED_0805_NOOUTLINE,
SPEAKER_7.5MM,SP1,Adafruit PyBadge-import-fps:BUZZER_SMT_7.5MM,
SPST_TACT-EVQQ2,SW1,Adafruit PyBadge-import-fps:EVQ-Q2_SMALLER,
WS2812B3535,"LED1,LED2,LED3,LED4,LED5",Adafruit PyBadge-import-fps:LED3535,
